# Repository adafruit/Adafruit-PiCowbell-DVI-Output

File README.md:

## Adafruit PiCowbell DVI Output for Pico - Works with HDMI Display PCB

<a href="http://www.adafruit.com/products/5745"><br/>
Click here to purchase one from the Adafruit shop</a>

PCB files for the Adafruit PiCowbell DVI Output for Pico - Works with HDMI Display. 

Format is EagleCAD schematic and board layout
* https://www.adafruit.com/product/5745

### Description

Ding dong! Hear that? It's the PiCowbell ringing, letting you know that the new Adafruit PiCowbell DVI Output for Pico is in stock and ready to display images and graphics from a microcontroller directly to an HDMI monitor or television! Note it doesn't do audio, just graphics.

The PiCowbell DVI is the same size and shape as a Pico and is intended to socket underneath to make your next video output project super easy. Mini HDMI connector for use with standard HDMI cables? Yes! STEMMA QT / Qwiic connector for fast I2C? Indeed. Reset button & extra switch for restarting code or changing configuration? Bien sur.

The PiCowbell DVI provides you with:

* Right angle JST SH connector for I2C / Stemma QT / Qwiic connection. Provides 3V, GND, IO4 (SDA), and IO5 (SCL). Also connected through to the HDMI sink (monitor) with level shifting, so the EDID can be read.
* Mini HDMI connector for DVI output to any HDMI display or monitor.
	* GPIO6: D2+
	* GPIO7: D2-
	* GPIO8: D1+
	* GPIO9: D1-
	* GPIO10: D0+
	* GPIO11: D0-
	* GPIO12: Clock +
	* GPIO13: Clock -
* Pin breakout for HDMI extras: Utility, CEC, and HotPlug pins
* Reset button - Press to restart your program
* Slide switch - On GPIO #3 for whatever purpose you wish.
* Many pads on the 'Bell has a duplicate hole pad next to it for solder-jumpering
* The ground pads have white silkscreen rectangles to easily identify
* Gold-plated pads for easy soldering

In Arduino, which is what we recommend, we use our fork of PicoDVI to create an internal framebuffer of 320x240 or 400x240 16-bit pixels that is then continuously blitted out as pixel-doubled 640x480 or 800x480 digital video. Whatever you 'draw' to the internal memory framebuffer appears instantly on the digital display in crisp color. Since the library is a subclass of AdafruitGFX, it'll be familiar to folks who have used our TFT or OLED displays before. 

There's also DVI output support in CircuitPython as of 8.1.0b2 - but note that it uses a lot of memory so in particular if you want to use PicoW with WiFi support, you'll likely only be able to get away with monochrome display.

Note that the DVI video generation uses one full core, both PIOs and 150K (320x240) or 190K (400x240) of SRAM. It's kinda maxed out so be aware of the remaining resource limitations.

We also connected the HDMI-connectors I2C pins to the SDA/SCL of the Pico (through a safe level shifter) so you can read the EDID EEPROM of displays, and have broken out the CEC and Utility pads. The Hot Plug Detect pin is also available. Read this pin to know when a display has been connected!

Each order comes with an assembled PCB and header. You will need to solder in the header yourself, but it's a quick task.

Please Note! There are a lot of possible configurations, and we stock various headers depending on how you want to solder and attach. Especially if you want the Pico on top so that the BOOTSEL button and LED are accessible.

1. Use the Pico Stacking Headers if you want to be able to plug into a breadboard or other accessory with sockets.
2. Use the Pico Socket Headers if you want to plug directly in and have a nice solid connection that doesn't have any poking-out-bits.
3. Use the Short Socket Headers for a very slim but pluggable design; note that you'll want to trim down the Pico's headers or use the short plug headers on the Pico to have a skinny sandwich.
4. Solder the PCB directly to the Pico headers - of course, this is very compact and inexpensive, but you won't be able to remove the PiCowbell.

### License

Adafruit invests time and resources providing this open source design, please support Adafruit and open-source hardware by purchasing products from [Adafruit](https://www.adafruit.com)!

Designed by Limor Fried/Ladyada for Adafruit Industries.

Creative Commons Attribution/Share-Alike, all text above must be included in any redistribution. 
See license.txt for additional details.

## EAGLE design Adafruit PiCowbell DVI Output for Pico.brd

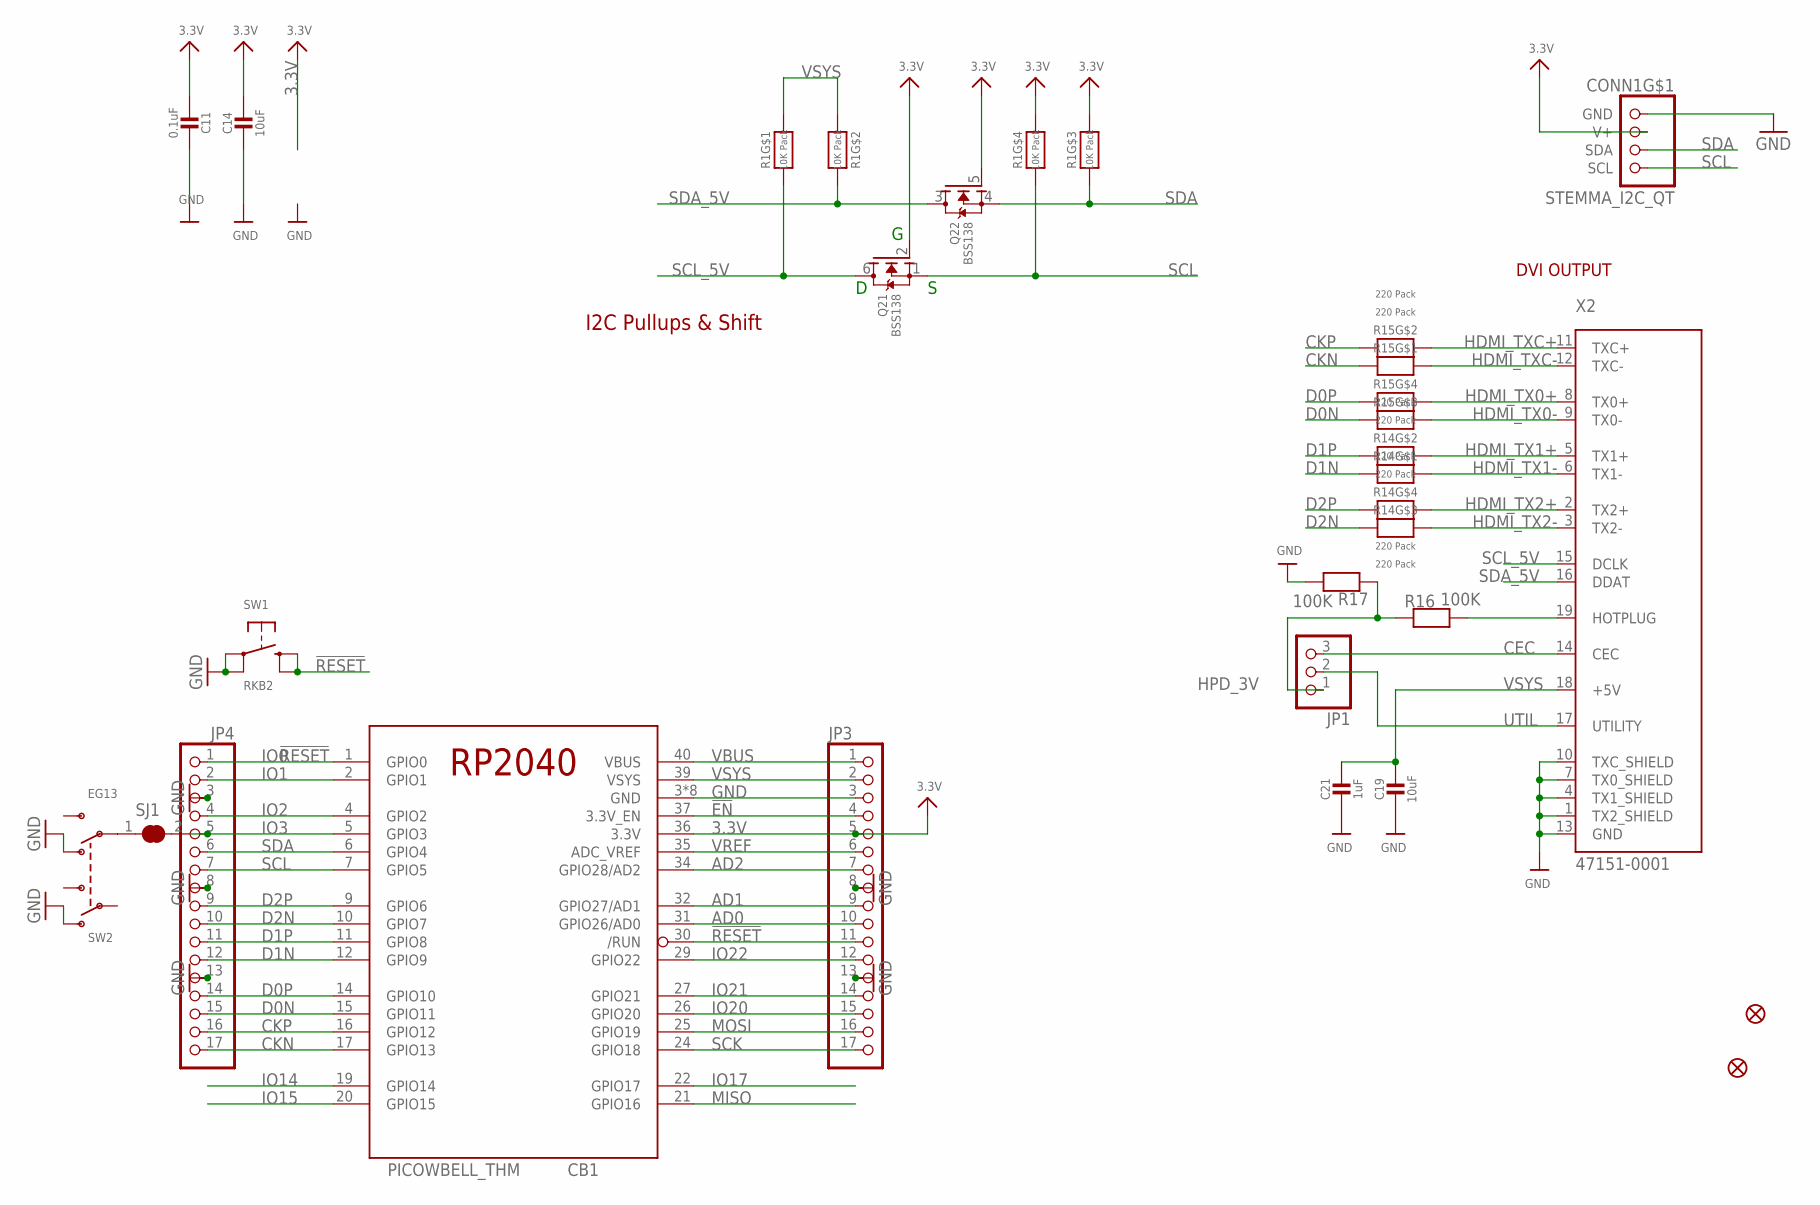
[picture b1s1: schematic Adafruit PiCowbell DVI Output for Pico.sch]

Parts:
C11: 0.1uF; 0603-NO
C14, C19: 10uF; 0805-NO
C21: 1uF; 0603-NO
CB1: PICOWBELL_THM
CONN1: STEMMA_I2C_QT; JST_SH4
FID1, FID2: FIDUCIAL_1MM
JP1: HEADER-1X3ROUND; 1X03_ROUND
JP3, JP4: HEADER-1X17; 1X17_ROUND70
Q2: BSS138; SOT363
R1: 10K Pack; RESPACK_4X0603
R14, R15: 220 Pack; RESPACK_4X0603
R16, R17: 100K; 0603-NO
SJ1: SOLDERJUMPER_CLOSED; SOLDERJUMPER_CLOSEDWIRE
SW1: RKB2; BTN_RKB2_4.6X2.8
SW2: EG13; EG1390
X2: 47151-0001; MINIHDMI_CNCTECH

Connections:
3.3V: C11.2, C14.1, CB1.36 (3.3V), CONN1.2 (V+), JP3.5, Q2.2 (G), Q2.5 (G), R1.5 (2), R1.6 (2)
!EN: CB1.37 (3.3V_EN), JP3.4
!RESET: CB1.30 (/RUN), JP3.11, SW1.B (S), SW1.B' (S1)
AD0: CB1.31 (GPIO26/AD0), JP3.10
AD1: CB1.32 (GPIO27/AD1), JP3.9
AD2: CB1.34 (GPIO28/AD2), JP3.7
CEC: JP1.3, X2.14 (CEC)
CKN: CB1.17 (GPIO13), JP4.17, R15.8 (2)
CKP: CB1.16 (GPIO12), JP4.16, R15.7 (2)
D0N: CB1.15 (GPIO11), JP4.15, R15.6 (2)
D0P: CB1.14 (GPIO10), JP4.14, R15.5 (2)
D1N: CB1.12 (GPIO9), JP4.12, R14.8 (2)
D1P: CB1.11 (GPIO8), JP4.11, R14.7 (2)
D2N: CB1.10 (GPIO7), JP4.10, R14.6 (2)
D2P: CB1.9 (GPIO6), JP4.9, R14.5 (2)
GND: C11.1, C14.2, C19.2, C21.2, CB1.3 (GND), CB1.8 (GND), CB1.13 (GND), CB1.18 (GND), CB1.23 (GND), CB1.28 (GND), CB1.33 (GND), CB1.38 (GND), CONN1.1 (GND), JP3.3, JP3.8, JP3.13, JP4.3, JP4.8, JP4.13, R17.2, SW1.A, SW1.A' (P1), SW2.O1, SW2.O2, X2.1 (TX2_SHIELD), X2.4 (TX1_SHIELD), X2.7 (TX0_SHIELD), X2.10 (TXC_SHIELD), X2.13 (GND), X2.MNT1 (GND), X2.MNT2 (GND), X2.MNT3 (GND), X2.MNT4 (GND)
HDMI_TX0+: R15.4 (1), X2.8 (TX0+)
HDMI_TX0-: R15.3 (1), X2.9 (TX0-)
HDMI_TX1+: R14.2 (1), X2.5 (TX1+)
HDMI_TX1-: R14.1, X2.6 (TX1-)
HDMI_TX2+: R14.4 (1), X2.2 (TX2+)
HDMI_TX2-: R14.3 (1), X2.3 (TX2-)
HDMI_TXC+: R15.2 (1), X2.11 (TXC+)
HDMI_TXC-: R15.1, X2.12 (TXC-)
HPD: R16.2, X2.19 (HOTPLUG)
HPD_3V: JP1.1, R16.1, R17.1
IO0: CB1.1 (GPIO0), JP4.1
IO1: CB1.2 (GPIO1), JP4.2
IO2: CB1.4 (GPIO2), JP4.4
IO3: CB1.5 (GPIO3), JP4.5, SJ1.2
IO14: CB1.19 (GPIO14)
IO15: CB1.20 (GPIO15)
IO17: CB1.22 (GPIO17)
IO20: CB1.26 (GPIO20), JP3.15
IO21: CB1.27 (GPIO21), JP3.14
IO22: CB1.29 (GPIO22), JP3.12
MISO: CB1.21 (GPIO16)
MOSI: CB1.25 (GPIO19), JP3.16
unnamed: SJ1.1, SW2.P2
SCK: CB1.24 (GPIO18), JP3.17
SCL: CB1.7 (GPIO5), CONN1.4 (SCL), JP4.7, Q2.1 (S), R1.4 (1)
SCL_5V: Q2.6 (D), R1.8 (2), X2.15 (DCLK)
SDA: CB1.6 (GPIO4), CONN1.3 (SDA), JP4.6, Q2.4 (S), R1.3 (1)
SDA_5V: Q2.3 (D), R1.7 (2), X2.16 (DDAT)
UTIL: JP1.2, X2.17 (UTILITY)
VBUS: CB1.40 (VBUS), JP3.1
VREF: CB1.35 (ADC_VREF), JP3.6
VSYS: C19.1, C21.1, CB1.39 (VSYS), JP3.2, R1.1, R1.2 (1), X2.18 (+5V)

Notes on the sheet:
DVI OUTPUT
I2C Pullups & Shift

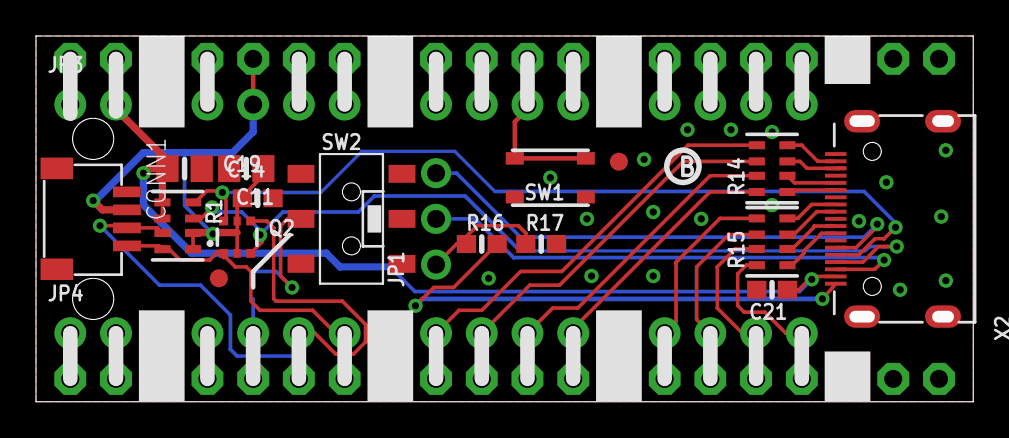
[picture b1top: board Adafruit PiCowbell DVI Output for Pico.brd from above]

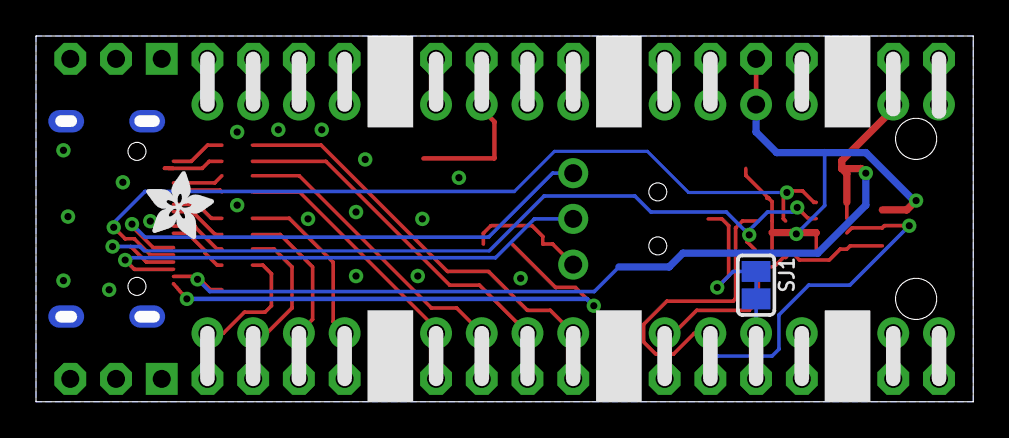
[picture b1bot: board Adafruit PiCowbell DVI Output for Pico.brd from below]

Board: 2 copper layers, 51.4 x 19.7 mm, 97 parts (39 on the bottom side), 44 nets.

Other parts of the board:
FRAME: ADAFRUIT_3.5MM
PLABEL36: PLABEL36
PLABEL37: PLABEL37
PLABEL38: PLABEL38
PLABEL39: PLABEL39
PLABEL40: PLABEL40
PLABEL41: PLABEL41
PLABEL42: PLABEL42
PLABEL43: PLABEL43
PLABEL44: PLABEL44
PLABEL45: PLABEL45
PLABEL46: PLABEL46
PLABEL47: PLABEL47
PLABEL48: PLABEL48
PLABEL49: PLABEL49
PLABEL50: PLABEL50
PLABEL51: PLABEL51
PLABEL52: PLABEL52
PLABEL53: PLABEL53
PLABEL54: PLABEL54
PLABEL55: PLABEL55
PLABEL56: PLABEL56
PLABEL57: PLABEL57
PLABEL58: PLABEL58
PLABEL59: PLABEL59
PLABEL60: PLABEL60
PLABEL61: PLABEL61
PLABEL62: PLABEL62
PLABEL63: PLABEL63
PLABEL64: PLABEL64
PLABEL65: PLABEL65
PLABEL66: PLABEL66
PLABEL67: PLABEL67
PLABEL68: PLABEL68
PLABEL69: PLABEL69
PLABEL70: PLABEL70
PLABEL71: PLABEL71
PLABEL72: PLABEL72
PLABEL73: PLABEL73
PLABEL74: PLABEL74
PLABEL75: PLABEL75
PLABEL76: PLABEL76
PLABEL77: PLABEL77
PLABEL78: PLABEL78
PLABEL79: PLABEL79
PLABEL80: PLABEL80
PLABEL81: PLABEL81
PLABEL82: PLABEL82
PLABEL83: PLABEL83
PLABEL84: PLABEL84
PLABEL85: PLABEL85
PLABEL86: PLABEL86
PLABEL87: PLABEL87
PLABEL88: PLABEL88
PLABEL89: PLABEL89
PLABEL90: PLABEL90
PLABEL91: PLABEL91
PLABEL92: PLABEL92
PLABEL93: PLABEL93
PLABEL94: PLABEL94
PLABEL95: PLABEL95
PLABEL96: PLABEL96
PLABEL97: PLABEL97
PLABEL98: PLABEL98
PLABEL99: PLABEL99
PLABEL100: PLABEL100
PLABEL101: PLABEL101
PLABEL102: PLABEL102
PLABEL103: PLABEL103
PLABEL104: PLABEL104
PLABEL105: PLABEL105
PLABEL106: PLABEL106
PLABEL107: PLABEL107
PLABEL108: PLABEL108
PLABEL109: PLABEL109
U$10: PCBFEAT-REV-040

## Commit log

2023-05-16 adding cookiecutter output

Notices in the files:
parts and their libraries:
microbuilder: This work is placed in the public domain, and may be freely used for commercial and non-commercial work with the following conditions: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
